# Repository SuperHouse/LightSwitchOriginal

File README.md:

Home Automation Light Switch
=============================
Copyright 2011-2012 SuperHouse Automation Pty Ltd  www.superhouse.tv  

Arduino shield light switch. This design is very old now: don't use it!

Features:

 * Positions for illuminated buttons
 * Can be assembled as 2-gang, 4-gang, and 6-gang

More information:

  http://www.superhouse.tv/

INSTALLATION
------------
The design is saved as an EAGLE project. EAGLE PCB design software is
available from www.cadsoftusa.com free for non-commercial use. To use
this project download it and place the directory containing these files
into the "eagle" directory on your computer. Then open EAGLE and
navigate to the project.

CREDITS
-------
Designed by Jonathan Oxer jon@oxer.com.au

DISTRIBUTION
------------
The specific terms of distribution of this project are governed by the
license referenced below.

LICENSE
-------
Licensed under the TAPR Open Hardware License (www.tapr.org/OHL).
The "license" folder within this repository also contains a copy of
this license in plain text format.

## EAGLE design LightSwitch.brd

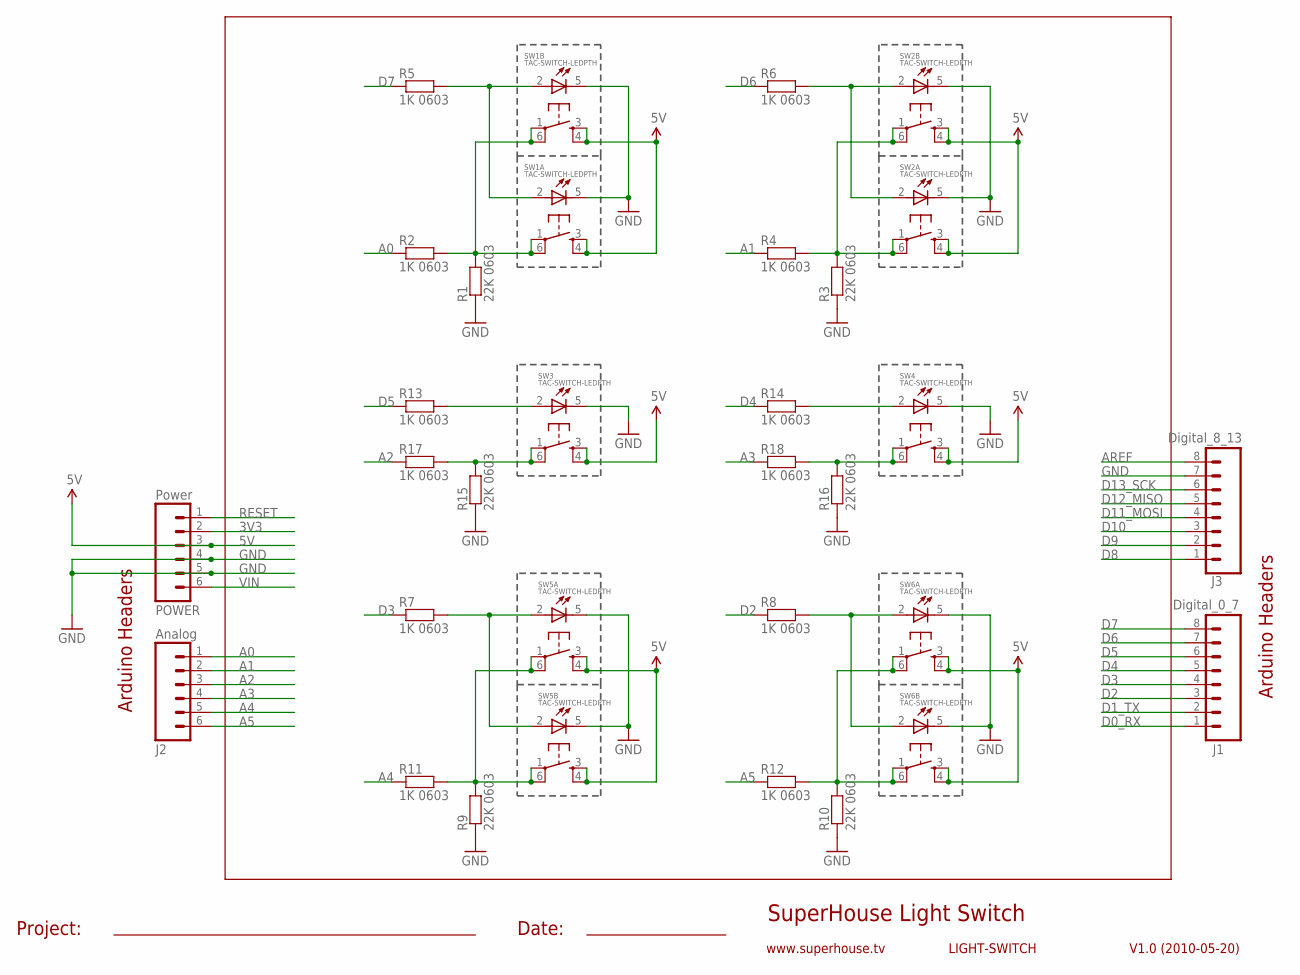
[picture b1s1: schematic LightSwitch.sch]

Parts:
J1: Digital_0_7; 1X08
J2: Analog; 1X06
J3: Digital_8_13; 1X08
POWER: Power; 1X06
R1, R3, R9, R10, R15, R16: 22K 0603; 0603
R2, R4, R5, R6, R7, R8, R11, R12, R13, R14, R17, R18: 1K 0603; 0603
SW1A, SW1B, SW2A, SW2B, SW3, SW4, SW5A, SW5B, SW6A, SW6B: TAC-SWITCH-LEDPTH; TACTILE-LED

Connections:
3V3: POWER.2
5V: POWER.3, SW1A.3, SW1A.4, SW1B.3, SW1B.4, SW2A.3, SW2A.4, SW2B.3, SW2B.4, SW3.3, SW3.4, SW4.3, SW4.4, SW5A.3, SW5A.4, SW5B.3, SW5B.4, SW6A.3, SW6A.4, SW6B.3, SW6B.4
A0: J2.1, R2.1
A1: J2.2, R4.1
A2: J2.3, R17.1
A3: J2.4, R18.1
A4: J2.5, R11.1
A5: J2.6, R12.1
AREF: J3.8
D0_RX: J1.1
D1_TX: J1.2
D2: J1.3, R8.1
D3: J1.4, R7.1
D4: J1.5, R14.1
D5: J1.6, R13.1
D6: J1.7, R6.1
D7: J1.8, R5.1
D8: J3.1
D9: J3.2
D10: J3.3
D11_MOSI: J3.4
D12_MISO: J3.5
D13_SCK: J3.6
GND: J3.7, POWER.4, POWER.5, R1.1, R3.1, R9.1, R10.1, R15.1, R16.1, SW1A.5 (C), SW1B.5 (C), SW2A.5 (C), SW2B.5 (C), SW3.5 (C), SW4.5 (C), SW5A.5 (C), SW5B.5 (C), SW6A.5 (C), SW6B.5 (C)
unnamed: R5.2, SW1A.2 (A), SW1B.2 (A)
unnamed: R6.2, SW2A.2 (A), SW2B.2 (A)
unnamed: R1.2, R2.2, SW1A.1, SW1A.6, SW1B.1, SW1B.6
unnamed: R13.2, SW3.2 (A)
unnamed: R14.2, SW4.2 (A)
unnamed: R7.2, SW5A.2 (A), SW5B.2 (A)
unnamed: R3.2, R4.2, SW2A.1, SW2A.6, SW2B.1, SW2B.6
unnamed: R8.2, SW6A.2 (A), SW6B.2 (A)
unnamed: R15.2, R17.2, SW3.1, SW3.6
unnamed: R16.2, R18.2, SW4.1, SW4.6
unnamed: R9.2, R11.2, SW5A.1, SW5A.6, SW5B.1, SW5B.6
unnamed: R10.2, R12.2, SW6A.1, SW6A.6, SW6B.1, SW6B.6
RESET: POWER.1
VIN: POWER.6

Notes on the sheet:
SuperHouse Light Switch
V1.0 (2010-05-20)
www.superhouse.tv
LIGHT-SWITCH
Arduino Headers
Project:
Date:

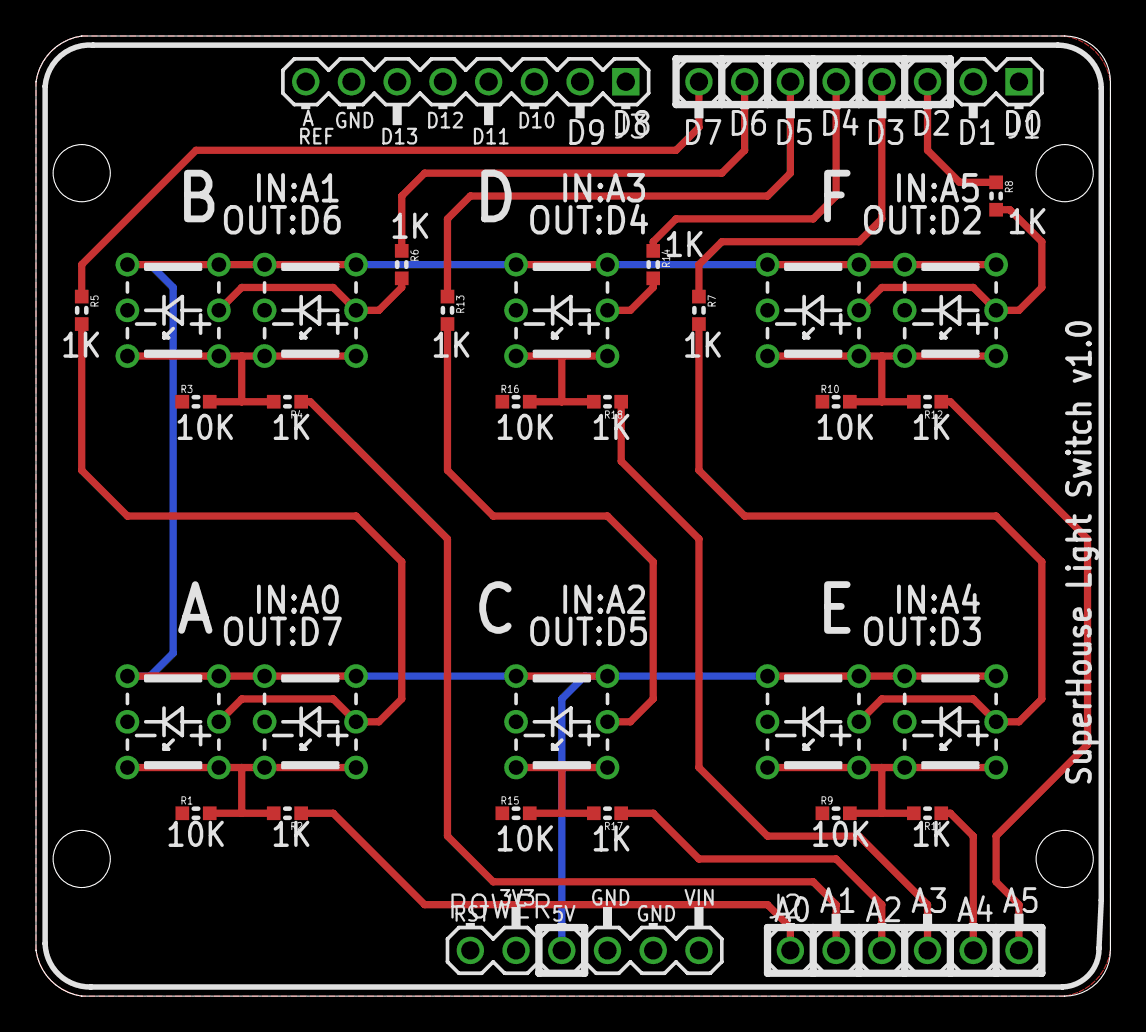
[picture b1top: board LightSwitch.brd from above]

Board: 2 copper layers, 59.7 x 53.3 mm, 32 parts (0 on the bottom side), 26 nets.

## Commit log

2018-03-28 Project import

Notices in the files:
LightSwitch.brd:
(c) 2011 SuperHouse Pty Ltd
